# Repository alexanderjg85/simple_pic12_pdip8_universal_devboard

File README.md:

# simple_pic12_pdip8_universal_devboard
A simple development board with an LED and GPIOs on Pin headers. Includes an ICSP Header and selectable dual power supply with a screw terminal

## Project Structure
- **/hardware**: Contains the KiCad schematic and PCB layout files.
- **/firmware**: Contains the Microchip MPLAB  C/ASM source code.

## Programming Notes
- Designed for all **PIC12 8-PDIP Variants with Flashmemory** microcontrollers.
- Programmed using **Microchip MPLAB** and an **PicKit 2/3** programmer. 
- *Note:* The PicKit Programmer can power the board. Make sure to choose appropriate Voltage 3.3 V or 5V and make sure that the board is jumpered correctly, if powered by external power supply. 

## License / Lizenz

This project is dual-licensed / Dieses Projekt ist dual-lizenziert:

* **Hardware (Schematic, PCB Layout):** Licensed under the [CERN Open Hardware Licence Version 2 - Permissive (CERN-OHL-P)](LICENSE_HARDWARE.md).
* **Software (Firmware, Example Code):** Licensed under the [MIT License](LICENSE).

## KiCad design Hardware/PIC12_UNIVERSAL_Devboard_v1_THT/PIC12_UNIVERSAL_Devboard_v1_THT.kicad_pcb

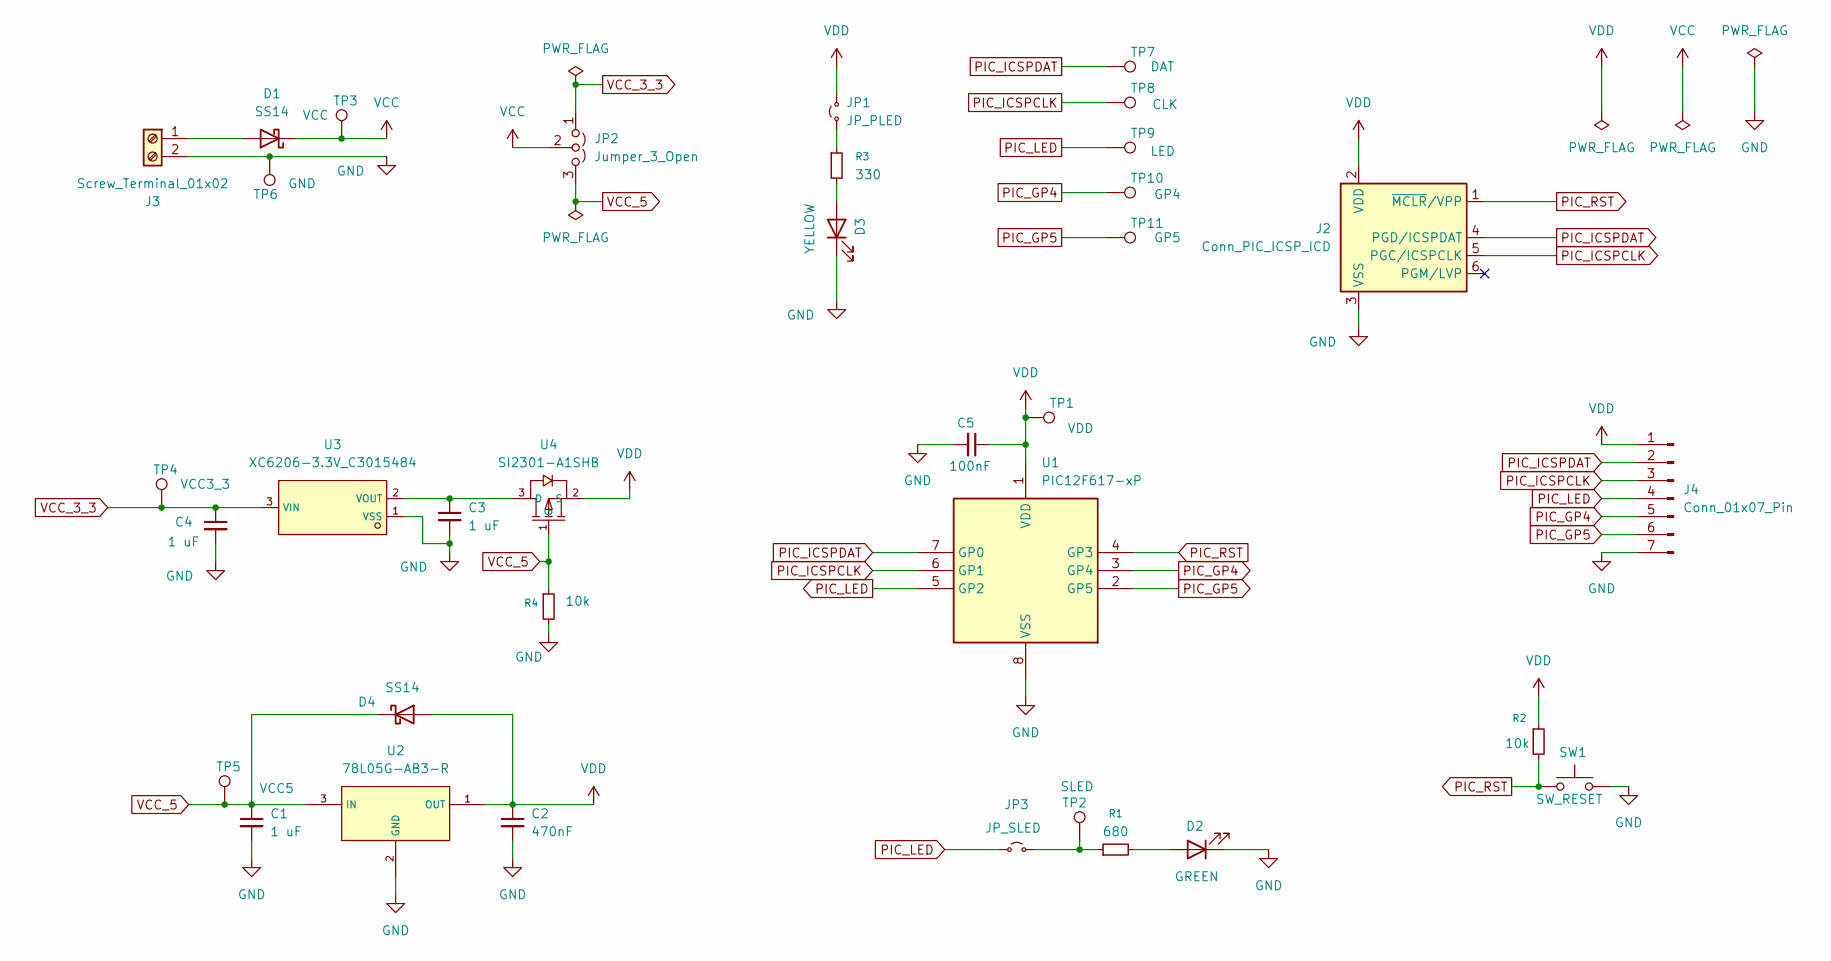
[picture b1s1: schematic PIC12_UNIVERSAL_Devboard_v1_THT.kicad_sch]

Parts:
C1, C3, C4: 1 uF; C6119929_C0805; LCSC C6119929
C2: 470nF; C13967_C0805; LCSC C13967
C5: 100nF; C49678_C0805; LCSC C49678
D1, D4: SS14; D_SMA_Handsoldering; LCSC C2480
D2: GREEN; LED_D3.0mm
D3: YELLOW; LED_D3.0mm
J2: Conn_PIC_ICSP_ICD; PinHeader_1x06_P2.54mm_Vertical
J3: Screw_Terminal_01x02; TerminalBlock_Phoenix_MKDS-1,5-2-5.08_1x02_P5.08mm_Horizont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
J4: Conn_01x07_Pin; PinHeader_1x07_P2.54mm_Vertical
JP1: JP_PLED; TestPoint_2Pads_Pitch2.54mm_Drill0.8mm
JP2: Jumper_3_Open; PinHeader_1x03_P2.54mm_Vertical
JP3: JP_SLED; TestPoint_2Pads_Pitch2.54mm_Drill0.8mm
R1: 680; R_1206_3216Metric_Pad1.30x1.75mm_HandSolder
R2, R4: 10k; R_1206_3216Metric_Pad1.30x1.75mm_HandSolder
R3: 330; R_1206_3216Metric_Pad1.30x1.75mm_HandSolder
SW1: SW_RESET; SW_SPST_PTS647_Sx38_Handsolder; MFR PN SWT0210-045026GSA
TP1: VDD; TestPoint_Pad_D1.5mm
TP2: SLED; TestPoint_Pad_D1.5mm
TP3: VCC; TestPoint_Pad_D1.5mm
TP4: VCC3_3; TestPoint_Pad_D1.5mm
TP5: VCC5; TestPoint_Pad_D1.5mm
TP6: GND; TestPoint_Pad_D1.5mm
TP7: DAT; TestPoint_Pad_D1.5mm
TP8: CLK; TestPoint_Pad_D1.5mm
TP9: LED; TestPoint_Pad_D1.5mm
TP10: GP4; TestPoint_Pad_D1.5mm
TP11: GP5; TestPoint_Pad_D1.5mm
U1: PIC12F617-xP; DIP-8_W7.62mm; MFR PN PIC12F17I/P
U2: 78L05G-AB3-R; C71136_SOT-89-3_L4_5-W2_5-P1_50-LS4_2-BR; LCSC C71136
U3: XC6206-3.3V_C3015484; C3015484_SOT-23-3_L2_9-W1_3-P0_95-LS2_4-BR; LCSC C3015484
U4: SI2301-A1SHB; C28642376_SOT-23-3_L2_9-W1_3-P1_90-LS2_4-BR; MFR PN SI2301-A1SHB; LCSC C28642376

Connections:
GND: C1.2, C2.2, C3.2, C4.2, C5.2, D2.1 (K), D3.1 (K), J2.3 (VSS), J3.2, J4.7, R4.2, SW1.2, TP6.1 (1_1), U1.8 (VSS), U2.2 (GND), U3.1 (VSS)
unnamed: D1.2 (A), J3.1
unnamed: D2.2 (A), R1.2
unnamed: D3.2 (A), R3.2
unnamed: JP1.1 (A), R3.1
unnamed: JP3.2 (B), R1.1, TP2.1 (1_1)
unnamed: C3.1, U3.2 (VOUT), U4.3 (D)
PIC_GP4: J4.5, TP10.1 (1_1), U1.3 (GP4)
PIC_GP5: J4.6, TP11.1 (1_1), U1.2 (GP5)
PIC_ICSPCLK: J2.5 (PGC/ICSPCLK), J4.3, TP8.1 (1_1), U1.6 (GP1)
PIC_ICSPDAT: J2.4 (PGD/ICSPDAT), J4.2, TP7.1 (1_1), U1.7 (GP0)
PIC_LED: J4.4, JP3.1 (A), TP9.1 (1_1), U1.5 (GP2)
PIC_RST: J2.1 (~MCLR/VPP), R2.2, SW1.1, U1.4 (GP3)
VCC: D1.1 (K), JP2.2 (C), TP3.1 (1_1)
VCC_3_3: C4.1, JP2.1 (A), TP4.1 (1_1), U3.3 (VIN)
VCC_5: C1.1, D4.1 (K), JP2.3 (B), R4.1, TP5.1 (1_1), U2.3 (IN), U4.1 (G)
VDD: C2.1, C5.1, D4.2 (A), J2.2 (VDD), J4.1, JP1.2 (B), R2.1, TP1.1 (1_1), U1.1 (VDD), U2.1 (OUT), U4.2 (S)

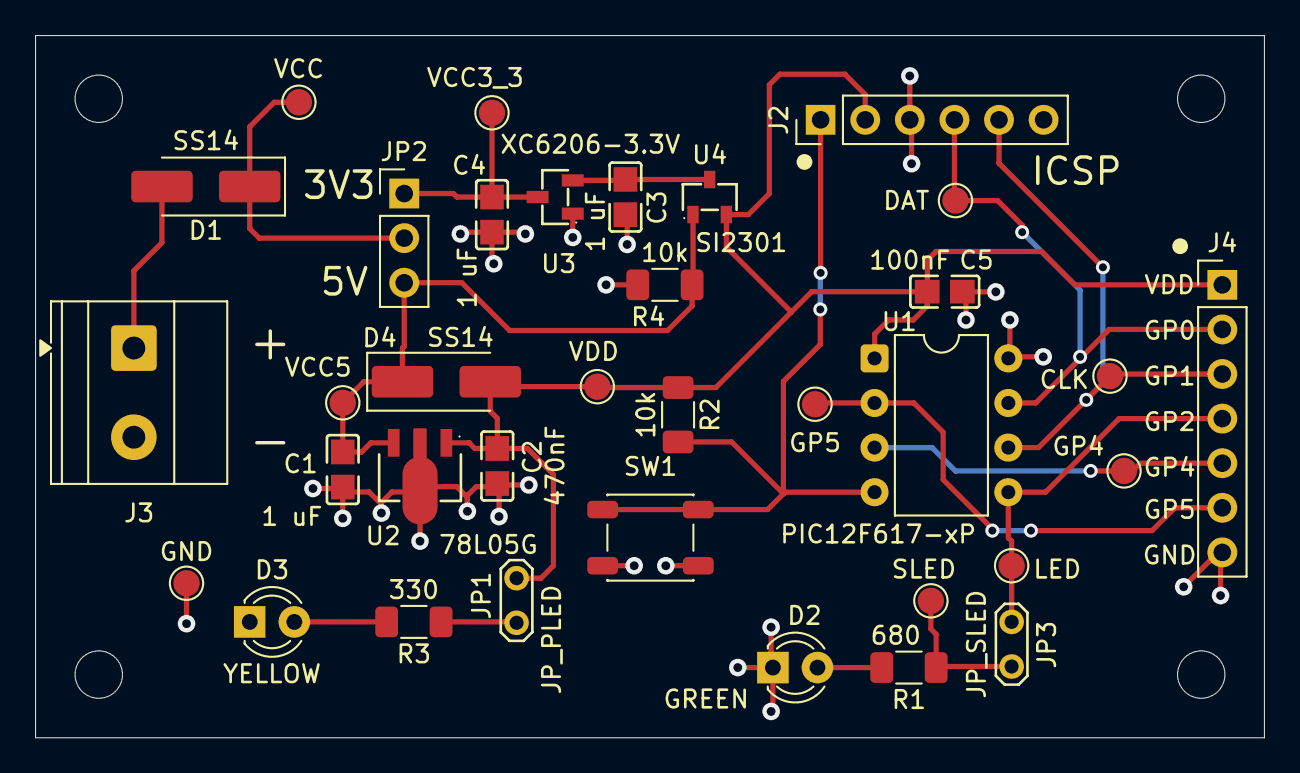
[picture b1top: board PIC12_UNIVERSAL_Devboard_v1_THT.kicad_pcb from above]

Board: 2 copper layers, 70.0 x 40.0 mm, 35 parts (0 on the bottom side), 17 nets.

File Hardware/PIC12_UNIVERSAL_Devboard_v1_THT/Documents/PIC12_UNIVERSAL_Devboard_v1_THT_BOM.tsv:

Reference	Qty	Value	Spec	Package	LCSC	MFR PN
C1,C3,C4	3	1 uF	 ±10% 50V	0805	C6119929	
C2	1	470nF	 ±10% 50V	0805	C13967	
C5	1	100nF	 ±10% 50V	0805	C49678	
D1,D4	2	SS14	30V 0.5A Schottky Diode	SMA	C2480	
D2	1	GREEN	LED GREEN	3 mm		
D3	1	YELLOW	LED YELLOW	3 mm		
J2	1	Conn_PIC_ICSP_ICD	Male / THT/ Vertical	2.54 mm 1x6		
J3	1	Screw_Terminal_01x02	Horizontal	5.08mm 1x2		
J4	1	Conn_01x07_Pin	Male / THT/ Vertical	2.54 mm 1x7		
JP1	1	JP_PLED	Male / THT/ Vertical	2.54 mm 1x2		
JP2	1	Jumper_3_Open	Male / THT/ Vertical	2.54 mm 1x3		
JP3	1	JP_SLED	Male / THT/ Vertical	2.54 mm 1x2		
R1	1	680	1% 125 mW	1206		
R2,R4	2	10k	1% 125 mW	1206		
R3	1	330	1% 125 mW	1206		
SW1	1	SW_RESET	H=5.0mm Tactile	4.5 x 4.5 SMD		
U1	1	PIC12F617-xP	8-Bit PIC 20 Mhz	PDIP-8		PIC12F17I/P
U2	1	78L05G-AB3-R	5V 0.1 A	SOT-89-3	C71136	
U3	1	XC6206-3.3V_C3015484	3.3V 0.25A	SOT23	C3015484	
U4	1	SI2301-A1SHB	P-Mos 20V 2.3A	SOT23	C28642376	SI2301-A1SHB
